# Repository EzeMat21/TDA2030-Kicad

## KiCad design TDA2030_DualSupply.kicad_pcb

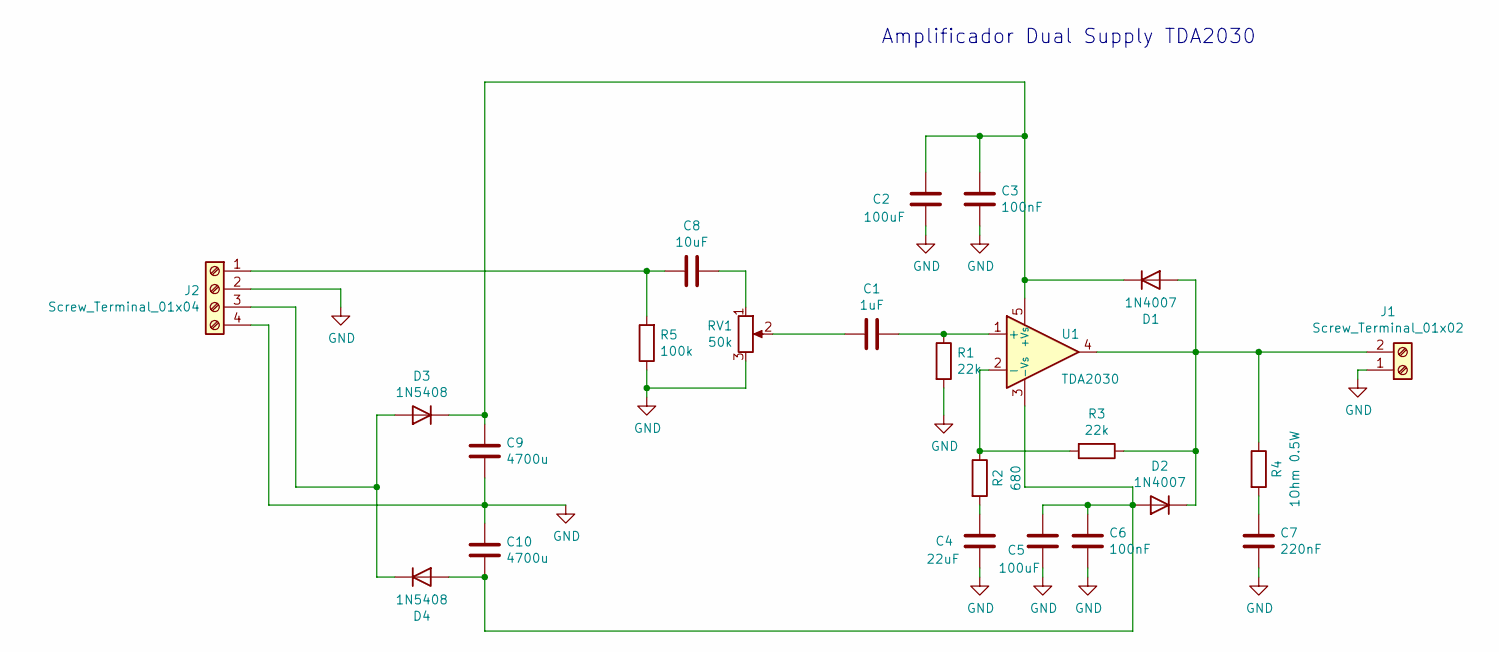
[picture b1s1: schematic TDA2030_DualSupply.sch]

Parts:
C1: 1uF; CP_Radial_D4.0mm_P2.00mm
C2, C5: 100uF; CP_Radial_D5.0mm_P2.50mm
C3, C6: 100nF; C_Disc_D3.8mm_W2.6mm_P2.50mm
C4: 22uF; CP_Radial_D4.0mm_P2.00mm
C7: 220nF; C_Rect_L16.5mm_W5.0mm_P15.00mm_MKT
C8: 10uF; CP_Radial_D5.0mm_P2.50mm
C9, C10: 4700u; CP_Radial_D18.0mm_P7.50mm
D1, D2: 1N4007; D_DO-41_SOD81_P10.16mm_Horizontal
D3, D4: 1N5408; D_DO-201AD_P15.24mm_Horizontal
J1: Screw_Terminal_01x02; PhoenixContact_MSTBA_2,5_2-G-5,08_1x02_P5.08mm_Horizontal
J2: Screw_Terminal_01x04; PhoenixContact_MCV_1,5_4-G-5.08_1x04_P5.08mm_Vertical
R1, R3: 22k; R_Axial_DIN0207_L6.3mm_D2.5mm_P10.16mm_Horizontal
R2: 680; R_Axial_DIN0207_L6.3mm_D2.5mm_P10.16mm_Horizontal
R4: 1Ohm 0.5W; R_Axial_DIN0309_L9.0mm_D3.2mm_P15.24mm_Horizontal
R5: 100k; R_Axial_DIN0207_L6.3mm_D2.5mm_P10.16mm_Horizontal
RV1: 50k; Potentiometer_Alps_RK163_Single_Horizontal
U1: TDA2030; TO-220-5_P3.4x3.7mm_StaggerOdd_Lead3.8mm_Vertical

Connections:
GND: C2.2, C3.2, C4.2, C5.2, C6.2, C7.2, C9.2, C10.1, J1.1, J2.2, J2.4, R1.2, R5.1, RV1.3
unnamed: C1.1, R1.1, U1.1 (+)
unnamed: C1.2, RV1.2
unnamed: C2.1, C3.1, C9.1, D1.1 (K), D3.1 (K), U1.5 (+Vs)
unnamed: C4.1, R2.2
unnamed: C7.1, R4.2
unnamed: C8.1, RV1.1
unnamed: C8.2, J2.1, R5.2
unnamed: C5.1, C6.1, C10.2, D2.2 (A), D4.2 (A), U1.3 (-Vs)
unnamed: D1.2 (A), D2.1 (K), J1.2, R3.1, R4.1, U1.4
unnamed: D3.2 (A), D4.1 (K), J2.3
unnamed: R2.1, R3.2, U1.2 (-)

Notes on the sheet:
Amplificador Dual Supply TDA2030

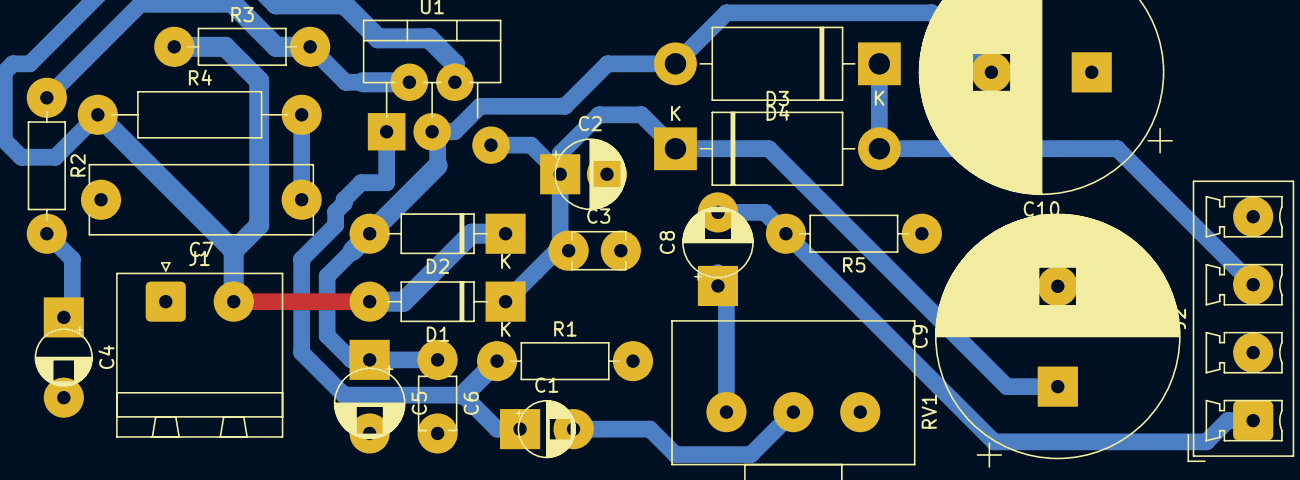
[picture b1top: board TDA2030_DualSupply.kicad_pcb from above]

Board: 2 copper layers, 23 parts (0 on the bottom side), 12 nets.

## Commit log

2024-12-09 primer commit
2024-12-09 segundo commit
2024-12-09 tercer commit
